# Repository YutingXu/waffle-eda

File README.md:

<picture>
  <source media="(prefers-color-scheme: dark)" srcset="brand/svg/waffle-lockup-eda-on-dark.svg">
  
</picture>

**A light, open schematic and PCB editor for macOS, Linux and Windows.**

Waffle is a local-first desktop EDA tool with Altium-style workflows, live design checks, a visual
history of your design, and an extension and AI interface built in from the start. It works offline,
needs no account and sends nothing anywhere unless you turn a feature on.

> **Status: 0.8 "Butter", early release.** Waffle is young. Expect rough edges and keep backups.
> Always check fabrication outputs in your manufacturer's viewer before ordering boards.

## Highlights

- **Familiar if you know Altium.** Key sequences, Active Bar, layer tabs, a rules editor, ECO and
  output jobs work the way you expect. KiCad and VS Code key presets are included.
- **Fast on big boards.** GPU drawing with a Canvas fallback, incremental redraw, live pours that
  preview while the exact fill is calculated, and online DRC that re-checks only what changed.
- **Schematic to fabrication.** Hierarchy and multichannel, variants, an interactive router with
  push-and-shove, differential pairs and length tuning, a stackup manager with rigid-flex, and
  Gerber X2, Excellon, ODB++, IPC-2581, STEP, pick-and-place, BOM and PDF outputs.
- **Bring your designs.** Open Altium, KiCad 6–9, EAGLE and EasyEDA projects. An import report
  lists what was converted and what was left out.
- **History you can see.** Visual undo history, object and file history, and side-by-side visual
  comparison of revisions, including Git. The `.waffle` format is readable, line-oriented JSON
  that diffs cleanly.
- **Make it yours.** Every command can be rebound, themes are editable, and sandboxed extensions can
  add commands, panels, checks and tools. The built-in SPICE simulator is itself an extension.
- **Works with AI assistants.** A bundled MCP server and CLI expose checks, generators and edits.
  AI edits arrive as proposals you review, never as silent changes.

| | |
| --- | --- |
|  |  |
|  |  |

## Install

Download the latest build from [Releases](../../releases).

| Platform | Steps |
| --- | --- |
| **macOS 12+** (Apple silicon, Intel) | Open the disk image and drag Waffle to Applications. The build is not notarized yet: on first launch, choose **Open Anyway** in System Settings → Privacy & Security (macOS 15+), or right-click Waffle and choose **Open** (macOS 12–14). |
| **Debian, Ubuntu** | `sudo apt install ./waffle-eda_<version>_all.deb`, then open Waffle EDA from the applications menu or run `waffle`. |
| **Windows 10 (1903+), 11** — *preview* | Extract the ZIP and run `Waffle.exe`. It is unsigned, so SmartScreen asks once (More info → Run anyway). |
| **Other Linux, or no install** | Run `./scripts/launch-linux.sh`, or open `app/index.html` from a release archive in a browser. |

New here? [Getting started](docs/getting-started.md) goes from an empty sheet to Gerbers.

## Extensions and AI

Extensions run in a sandboxed worker with no access to your files, network or the page. Each one
asks for the permissions it needs, such as reading the design, proposing edits, adding panels or
contacting one named server, and you can revoke any of them at any time. Edits go through the
same validated, undoable transactions as your own. See [Extensions](docs/extensions.md) and the
[API reference](docs/extension-api.md).

For AI assistants and CI, run the MCP server or the CLI:

```sh
python3 mcp/server.py --project board.waffle --cli run_output_job …
```

See [MCP and CLI](docs/mcp-and-cli.md).

## Privacy

- No telemetry, no account, no background network traffic.
- Network features are opt-in: supplier pricing, the AI Assistant, and extensions you allow to
  reach a named host.
- API keys never go into project files.
- Projects that carry an extension keep it blocked until you trust that exact package.

To report a vulnerability, see [SECURITY.md](SECURITY.md).

## Build from source

```sh
python3 scripts/prepare-assets.py   # once per fresh checkout (Python 3.9+, Rust for the engine)
./scripts/build-mac.sh              # macOS app (Xcode)
python3 scripts/build-deb.py        # Debian package
./scripts/build-windows.sh          # Windows ZIP (.NET 8 SDK)
node tests/run.cjs                  # regression suite (Node 18+)
```

More in the [user guide](docs/README.md).

## Contributing

Contributions are welcome, including ones written with AI tools. **Please open an issue before a
large change** so we can agree on the approach first. Read [CONTRIBUTING.md](CONTRIBUTING.md) for
the clean-room policy (no decompiled vendor software, no vendor libraries or documentation) and the
[Code of Conduct](CODE_OF_CONDUCT.md).

Waffle is a personal project, developed largely with AI coding agents. Feedback from people who
design real boards is the most useful contribution of all.

## License and disclaimer

Waffle EDA is released under the [MIT License](LICENSE). Bundled third-party components keep their
own licenses; see [THIRD_PARTY_NOTICES.md](THIRD_PARTY_NOTICES.md) or **Help → Licenses**.

Waffle is provided as is, without warranty of any kind. You are responsible for verifying any
design, check result or fabrication output before you build hardware with it.

Waffle EDA is an independent project, not affiliated with or endorsed by Altium LLC or any other
vendor. Altium® and Altium Designer® are trademarks of Altium LLC. KiCad, EAGLE, EasyEDA, VS Code,
Gerber and other names belong to their owners and are used only to describe compatibility.

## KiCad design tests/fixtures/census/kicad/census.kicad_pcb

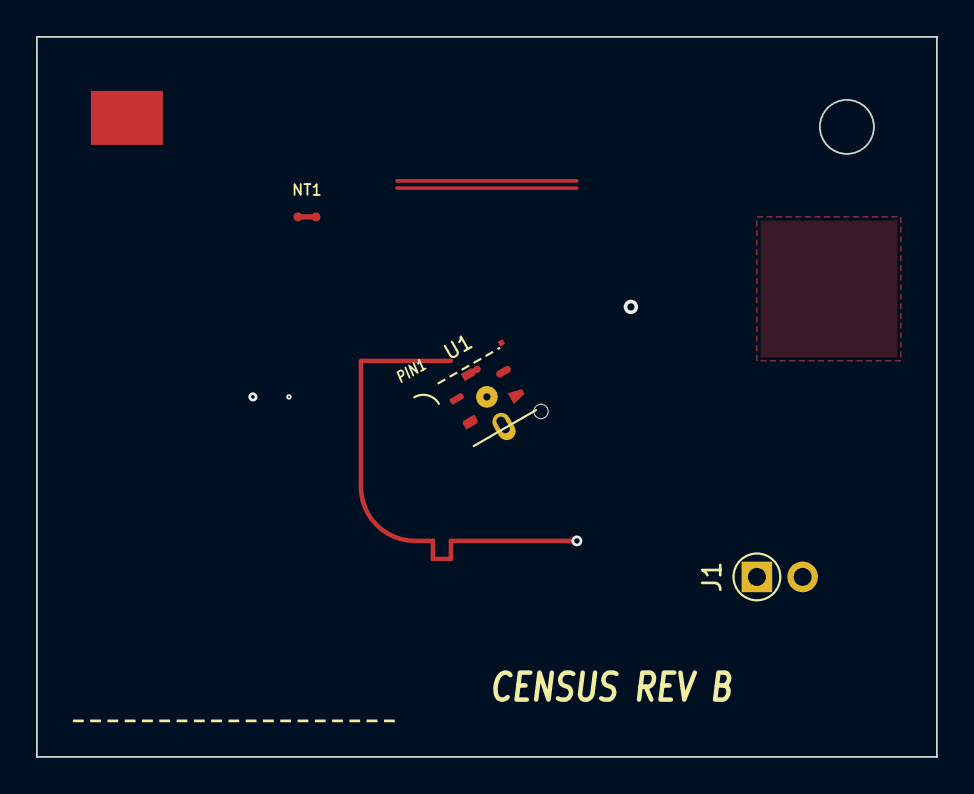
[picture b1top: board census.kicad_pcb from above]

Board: 4 copper layers, 50.0 x 40.0 mm, 4 parts (1 on the bottom side), 3 nets.

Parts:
J1: Conn_01x02; Header_1x02
NT1: NetTie; NetTie_2
R1: 22R; R_0402
U1: CENSUS-8; QFN-8_Custom

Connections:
GND: J1.2, NT1.1, R1.2, U1.5 (GND), U1.6 (EP)
SIG: R1.1, U1.4 (OUT), U1.7 (SENSE)
VCC: J1.1, U1.1 (VIN)
